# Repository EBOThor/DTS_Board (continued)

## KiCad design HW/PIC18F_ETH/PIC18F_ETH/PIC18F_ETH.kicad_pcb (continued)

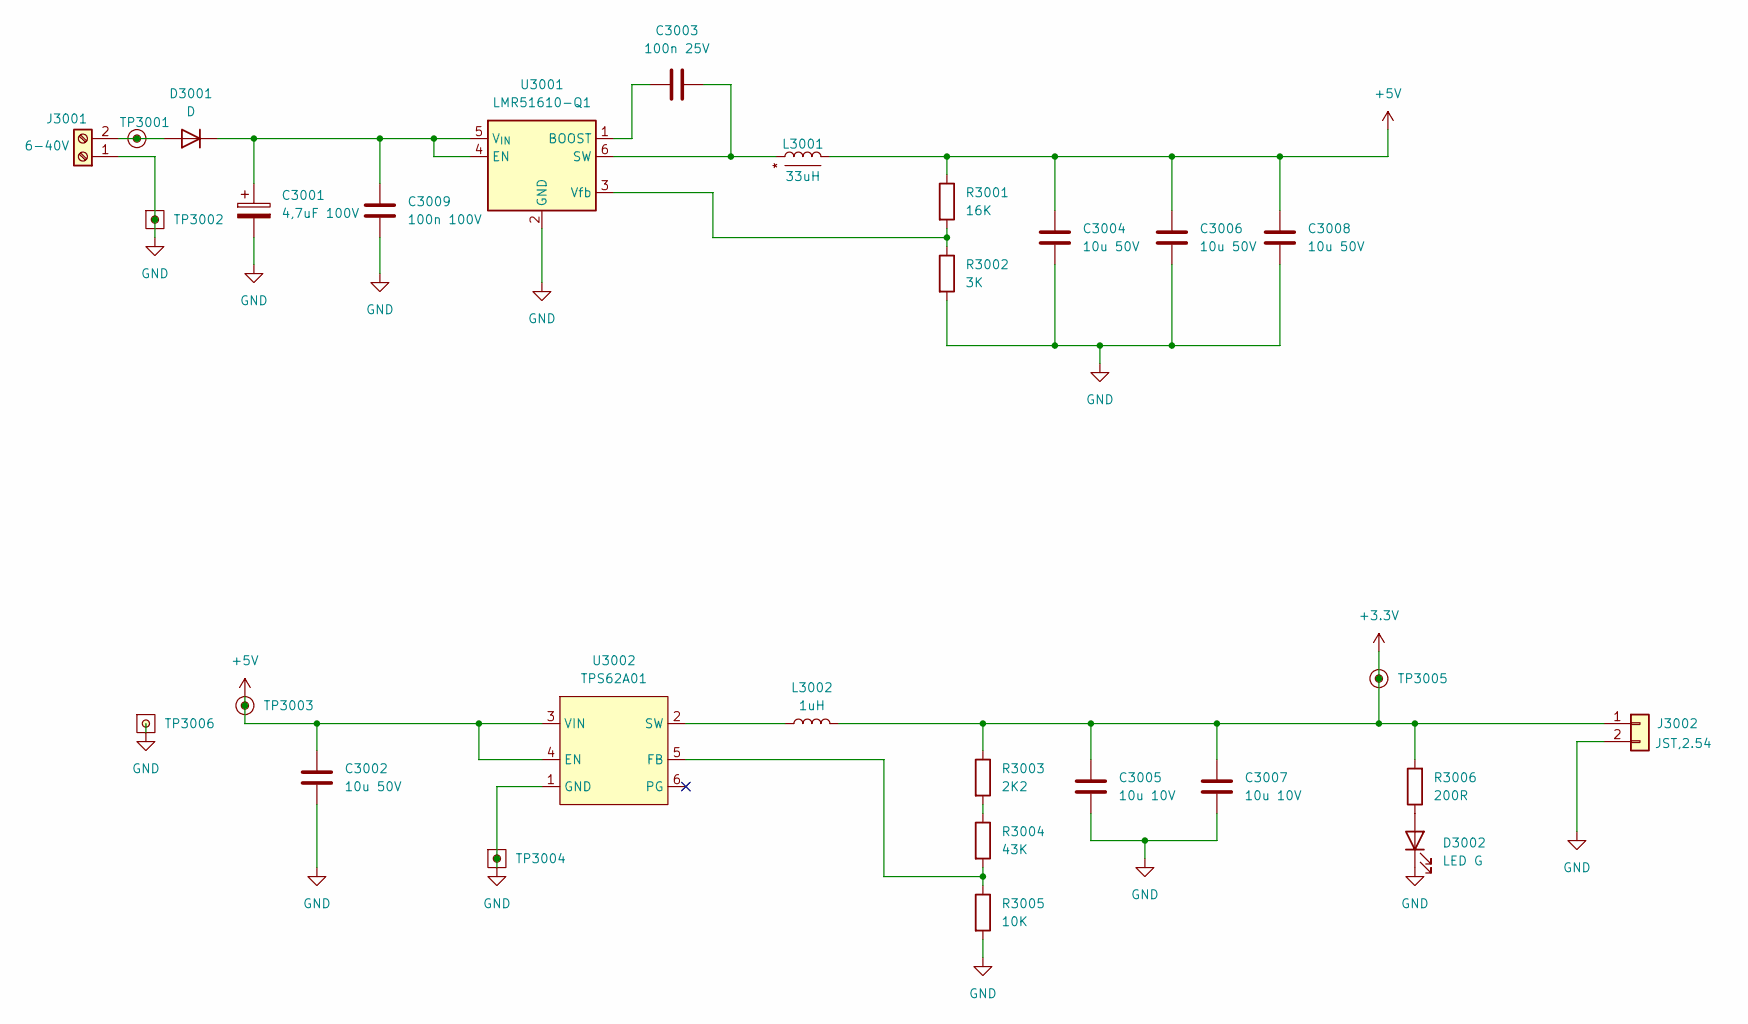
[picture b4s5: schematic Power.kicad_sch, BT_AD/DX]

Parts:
C3001: 4,7uF 100V; CP_Elec_4x3
C3002, C3004, C3006, C3008: 10u 50V; C_0603_1608Metric; MPN C;C;T1;S;P0603;NA
C3003: 100n 25V; C_0603_1608Metric; MPN C;C;T1;S;P0603;NA
C3005, C3007: 10u 10V; C_0603_1608Metric; MPN C;C;T1;S;P0603;NA
C3009: 100n 100V; C_0603_1608Metric; MPN C;M;100n;10p;100V;S;0603
D3001: D; D_0805_2012Metric
D3002: LED G; LED_0603_1608Metric; MPN D;LED;R;3V;25mA
J3001: 6-40V; Samtec_HPM-02-01-x-S_Straight_1x02_Pitch5.08mm
J3002: JST,2.54; JST_EH_B2B-EH-A_1x02_P2.50mm_Vertical; MPN JST 2 pin
L3001: 33uH; L_Bourns_SRR1208_12.7x12.7mm; MPN SRR1208-330YL
L3002: 1uH; L_0805_2012Metric; MPN CIGT201208EH1R0MNE
R3001: 16K; R_0603_1608Metric; MPN R;G;T1;S;P0603;NA
R3002: 3K; R_0603_1608Metric; MPN R;G;T1;S;P0603;NA
R3003: 2K2; R_0603_1608Metric; MPN R;G;T1;S;P0603;NA
R3004: 43K; R_0603_1608Metric; MPN R;G;T1;S;P0603;NA
R3005: 10K; R_0603_1608Metric; MPN R;G;T1;S;P0603;NA
R3006: 200R; R_0603_1608Metric; MPN R;G;T1;S;P0603;NA
TP3001, TP3003, TP3005: TestPoint; TestPoint_THTPad_D1.0mm_Drill0.5mm
TP3002, TP3004, TP3006: TestPoint; TestPoint_THTPad_1.0x1.0mm_Drill0.5mm
U3001: LMR51610-Q1; SOT-23-6; MPN LMR51610-Q1
U3002: TPS62A01; SOT-563; MPN TPS62A01

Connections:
+3.3V: C3005.1, C3007.1, J3002.1, L3002.2, R3003.1, R3006.2, TP3005.1; also elsewhere on the board
+5V: C3002.1, C3004.1, C3006.1, C3008.1, L3001.2, R3001.1, TP3003.1, U3002.3 (VIN), U3002.4 (EN); also elsewhere on the board
GND: C3001.2, C3002.2, C3004.2, C3005.2, C3006.2, C3007.2, C3008.2, C3009.2, D3002.1 (K), J3001.1, J3002.2, R3002.2, R3005.2, TP3002.1, TP3004.1, TP3006.1, U3001.2 (GND), U3002.1 (GND); also elsewhere on the board
unnamed: D3001.2 (A), J3001.2, TP3001.1
unnamed: C3001.1, C3009.1, D3001.1 (K), U3001.4 (EN), U3001.5 (V_{IN})
unnamed: D3002.2 (A), R3006.1
unnamed: R3003.2, R3004.1
unnamed: C3003.1, U3001.1 (BOOST)
unnamed: C3003.2, L3001.1, U3001.6 (SW)
unnamed: R3001.2, R3002.1, U3001.3 (Vfb)
unnamed: R3004.2, R3005.1, U3002.5 (FB)
unnamed: L3002.1, U3002.2 (SW)

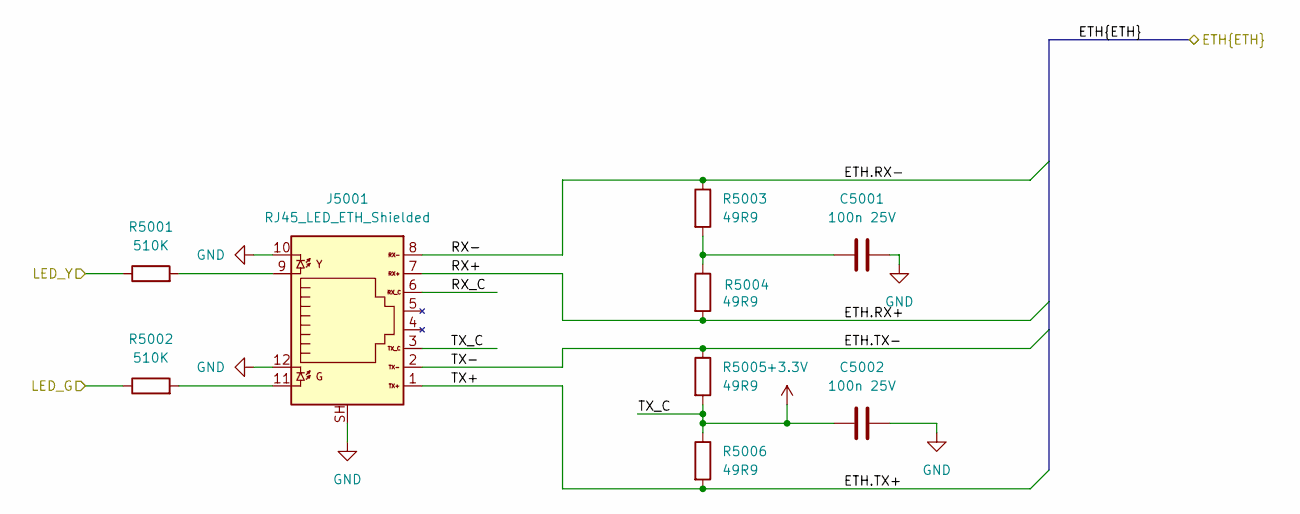
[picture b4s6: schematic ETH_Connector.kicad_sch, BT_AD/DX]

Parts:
C5001, C5002: 100n 25V; C_0603_1608Metric; MPN C;C;T1;S;P0603;NA
J5001: RJ45_LED_ETH_Shielded; RJ45_LED_Shield; MPN 41010276
R5001, R5002: 510K; R_0603_1608Metric; MPN R;G;T1;S;P0603;NA
R5003, R5004, R5005, R5006: 49R9; R_0603_1608Metric

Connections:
+3.3V: C5002.1, J5001.3, R5005.2, R5006.1; also elsewhere on the board
/ETH_Connector/ETH.RX+: J5001.7, R5004.2; also elsewhere on the board
/ETH_Connector/ETH.RX-: J5001.8, R5003.1; also elsewhere on the board
/ETH_Connector/ETH.TX+: J5001.1, R5006.2; also elsewhere on the board
/ETH_Connector/ETH.TX-: J5001.2, R5005.1; also elsewhere on the board
/ETH_Connector/RX_C: J5001.6
/LED_G: R5002.1; also elsewhere on the board
/LED_Y: R5001.1; also elsewhere on the board
GND: C5001.2, C5002.2, J5001.10, J5001.12, J5001.SH; also elsewhere on the board
unnamed: C5001.1, R5003.2, R5004.1
unnamed: J5001.9, R5001.2
unnamed: J5001.11, R5002.2

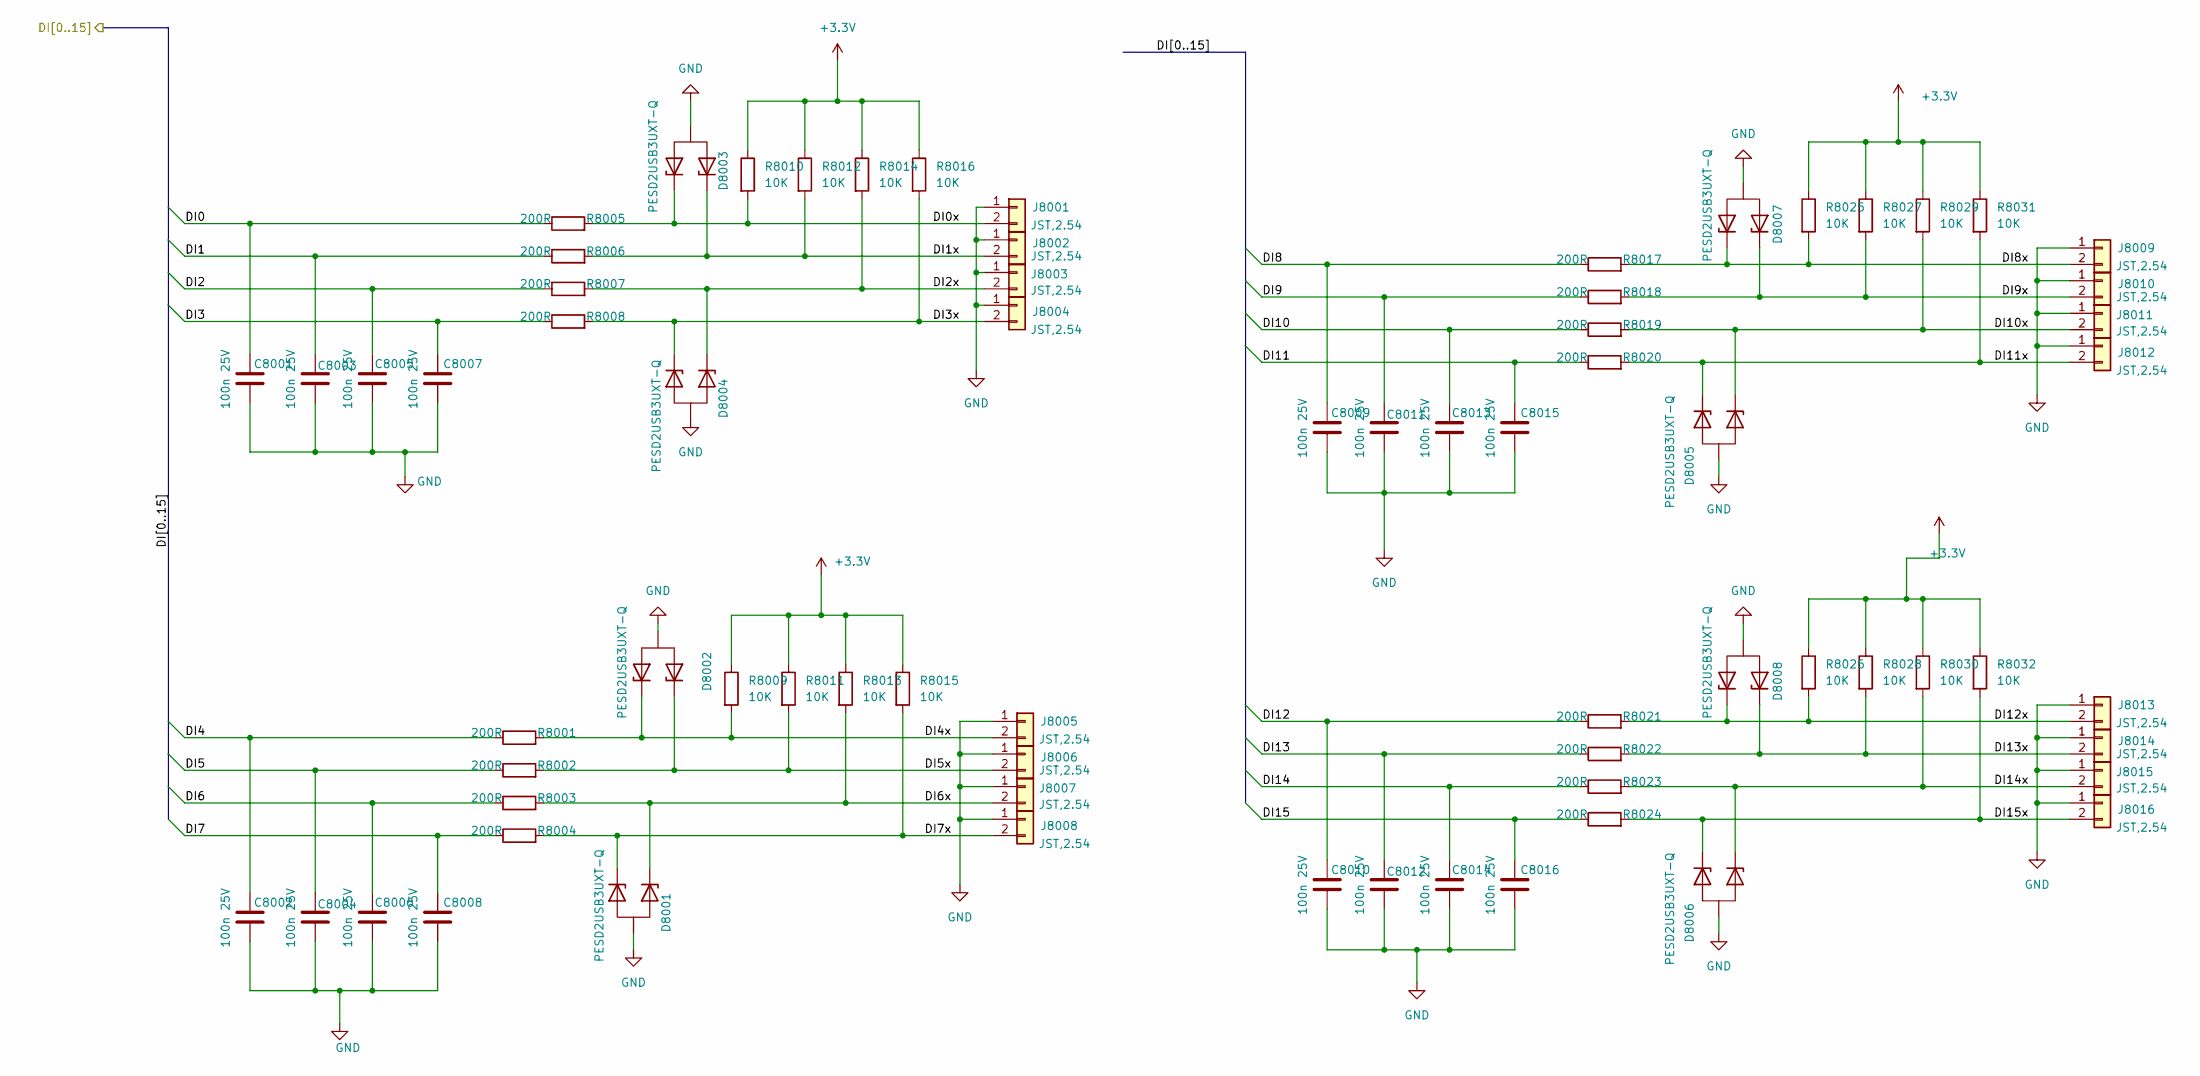
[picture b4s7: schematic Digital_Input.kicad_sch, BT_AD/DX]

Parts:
C8001, C8002, C8003, C8004, C8005, C8006, C8007, C8008, C8009, C8010, C8011, C8012, C8013, C8014, C8015, C8016: 100n 25V; C_0603_1608Metric; MPN C;C;T1;S;P0603;NA
D8001, D8002, D8003, D8004, D8005, D8006, D8007, D8008: PESD2USB3UXT-Q; SOT-23-3; MPN PESD2USB3UXT-Q
J8001, J8002, J8003, J8004, J8005, J8006, J8007, J8008, J8009, J8010, J8011, J8012, J8013, J8014, J8015, J8016: JST,2.54; JST_EH_B2B-EH-A_1x02_P2.50mm_Vertical; MPN JST 2 pin
R8001, R8002, R8003, R8004, R8005, R8006, R8007, R8008, R8017, R8018, R8019, R8020, R8021, R8022, R8023, R8024: 200R; R_0603_1608Metric; MPN R;G;T1;S;P0603;NA
R8009, R8010, R8011, R8012, R8013, R8014, R8015, R8016, R8025, R8026, R8027, R8028, R8029, R8030, R8031, R8032: 10K; R_0603_1608Metric; MPN R;G;T1;S;P0603;NA

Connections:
+3.3V: R8009.1, R8010.1, R8011.1, R8012.1, R8013.1, R8014.1, R8015.1, R8016.1, R8025.1, R8026.1, R8027.1, R8028.1, R8029.1, R8030.1, R8031.1, R8032.1; also elsewhere on the board
/IO_core/DI0: C8001.1, R8005.1; also elsewhere on the board
/IO_core/DI1: C8003.1, R8006.1; also elsewhere on the board
/IO_core/DI2: C8005.1, R8007.1; also elsewhere on the board
/IO_core/DI3: C8007.1, R8008.1; also elsewhere on the board
/IO_core/DI4: C8002.1, R8001.1; also elsewhere on the board
/IO_core/DI5: C8004.1, R8002.1; also elsewhere on the board
/IO_core/DI6: C8006.1, R8003.1; also elsewhere on the board
/IO_core/DI7: C8008.1, R8004.1; also elsewhere on the board
/IO_core/DI8: C8009.1, R8017.1; also elsewhere on the board
/IO_core/DI9: C8011.1, R8018.1; also elsewhere on the board
/IO_core/DI10: C8013.1, R8019.1; also elsewhere on the board
/IO_core/DI11: C8015.1, R8020.1; also elsewhere on the board
/IO_core/DI12: C8010.1, R8021.1; also elsewhere on the board
/IO_core/DI13: C8012.1, R8022.1; also elsewhere on the board
/IO_core/DI14: C8014.1, R8023.1; also elsewhere on the board
/IO_core/DI15: C8016.1, R8024.1; also elsewhere on the board
/IO_core/Digital Input/DI0x: D8003.1 (K1), J8001.2, R8005.2, R8010.2
/IO_core/Digital Input/DI1x: D8003.2 (K2), J8002.2, R8006.2, R8012.2
/IO_core/Digital Input/DI2x: D8004.1 (K1), J8003.2, R8007.2, R8014.2
/IO_core/Digital Input/DI3x: D8004.2 (K2), J8004.2, R8008.2, R8016.2
/IO_core/Digital Input/DI4x: D8002.1 (K1), J8005.2, R8001.2, R8009.2
/IO_core/Digital Input/DI5x: D8002.2 (K2), J8006.2, R8002.2, R8011.2
/IO_core/Digital Input/DI6x: D8001.1 (K1), J8007.2, R8003.2, R8013.2
/IO_core/Digital Input/DI7x: D8001.2 (K2), J8008.2, R8004.2, R8015.2
/IO_core/Digital Input/DI8x: D8007.1 (K1), J8009.2, R8017.2, R8025.2
/IO_core/Digital Input/DI9x: D8007.2 (K2), J8010.2, R8018.2, R8027.2
/IO_core/Digital Input/DI10x: D8005.1 (K1), J8011.2, R8019.2, R8029.2
/IO_core/Digital Input/DI11x: D8005.2 (K2), J8012.2, R8020.2, R8031.2
/IO_core/Digital Input/DI12x: D8008.1 (K1), J8013.2, R8021.2, R8026.2
/IO_core/Digital Input/DI13x: D8008.2 (K2), J8014.2, R8022.2, R8028.2
/IO_core/Digital Input/DI14x: D8006.1 (K1), J8015.2, R8023.2, R8030.2
/IO_core/Digital Input/DI15x: D8006.2 (K2), J8016.2, R8024.2, R8032.2
GND: C8001.2, C8002.2, C8003.2, C8004.2, C8005.2, C8006.2, C8007.2, C8008.2, C8009.2, C8010.2, C8011.2, C8012.2, C8013.2, C8014.2, C8015.2, C8016.2, D8001.3 (CA), D8002.3 (CA), D8003.3 (CA), D8004.3 (CA), D8005.3 (CA), D8006.3 (CA), D8007.3 (CA), D8008.3 (CA), J8001.1, J8002.1, J8003.1, J8004.1, J8005.1, J8006.1, J8007.1, J8008.1, J8009.1, J8010.1, J8011.1, J8012.1, J8013.1, J8014.1, J8015.1, J8016.1; also elsewhere on the board

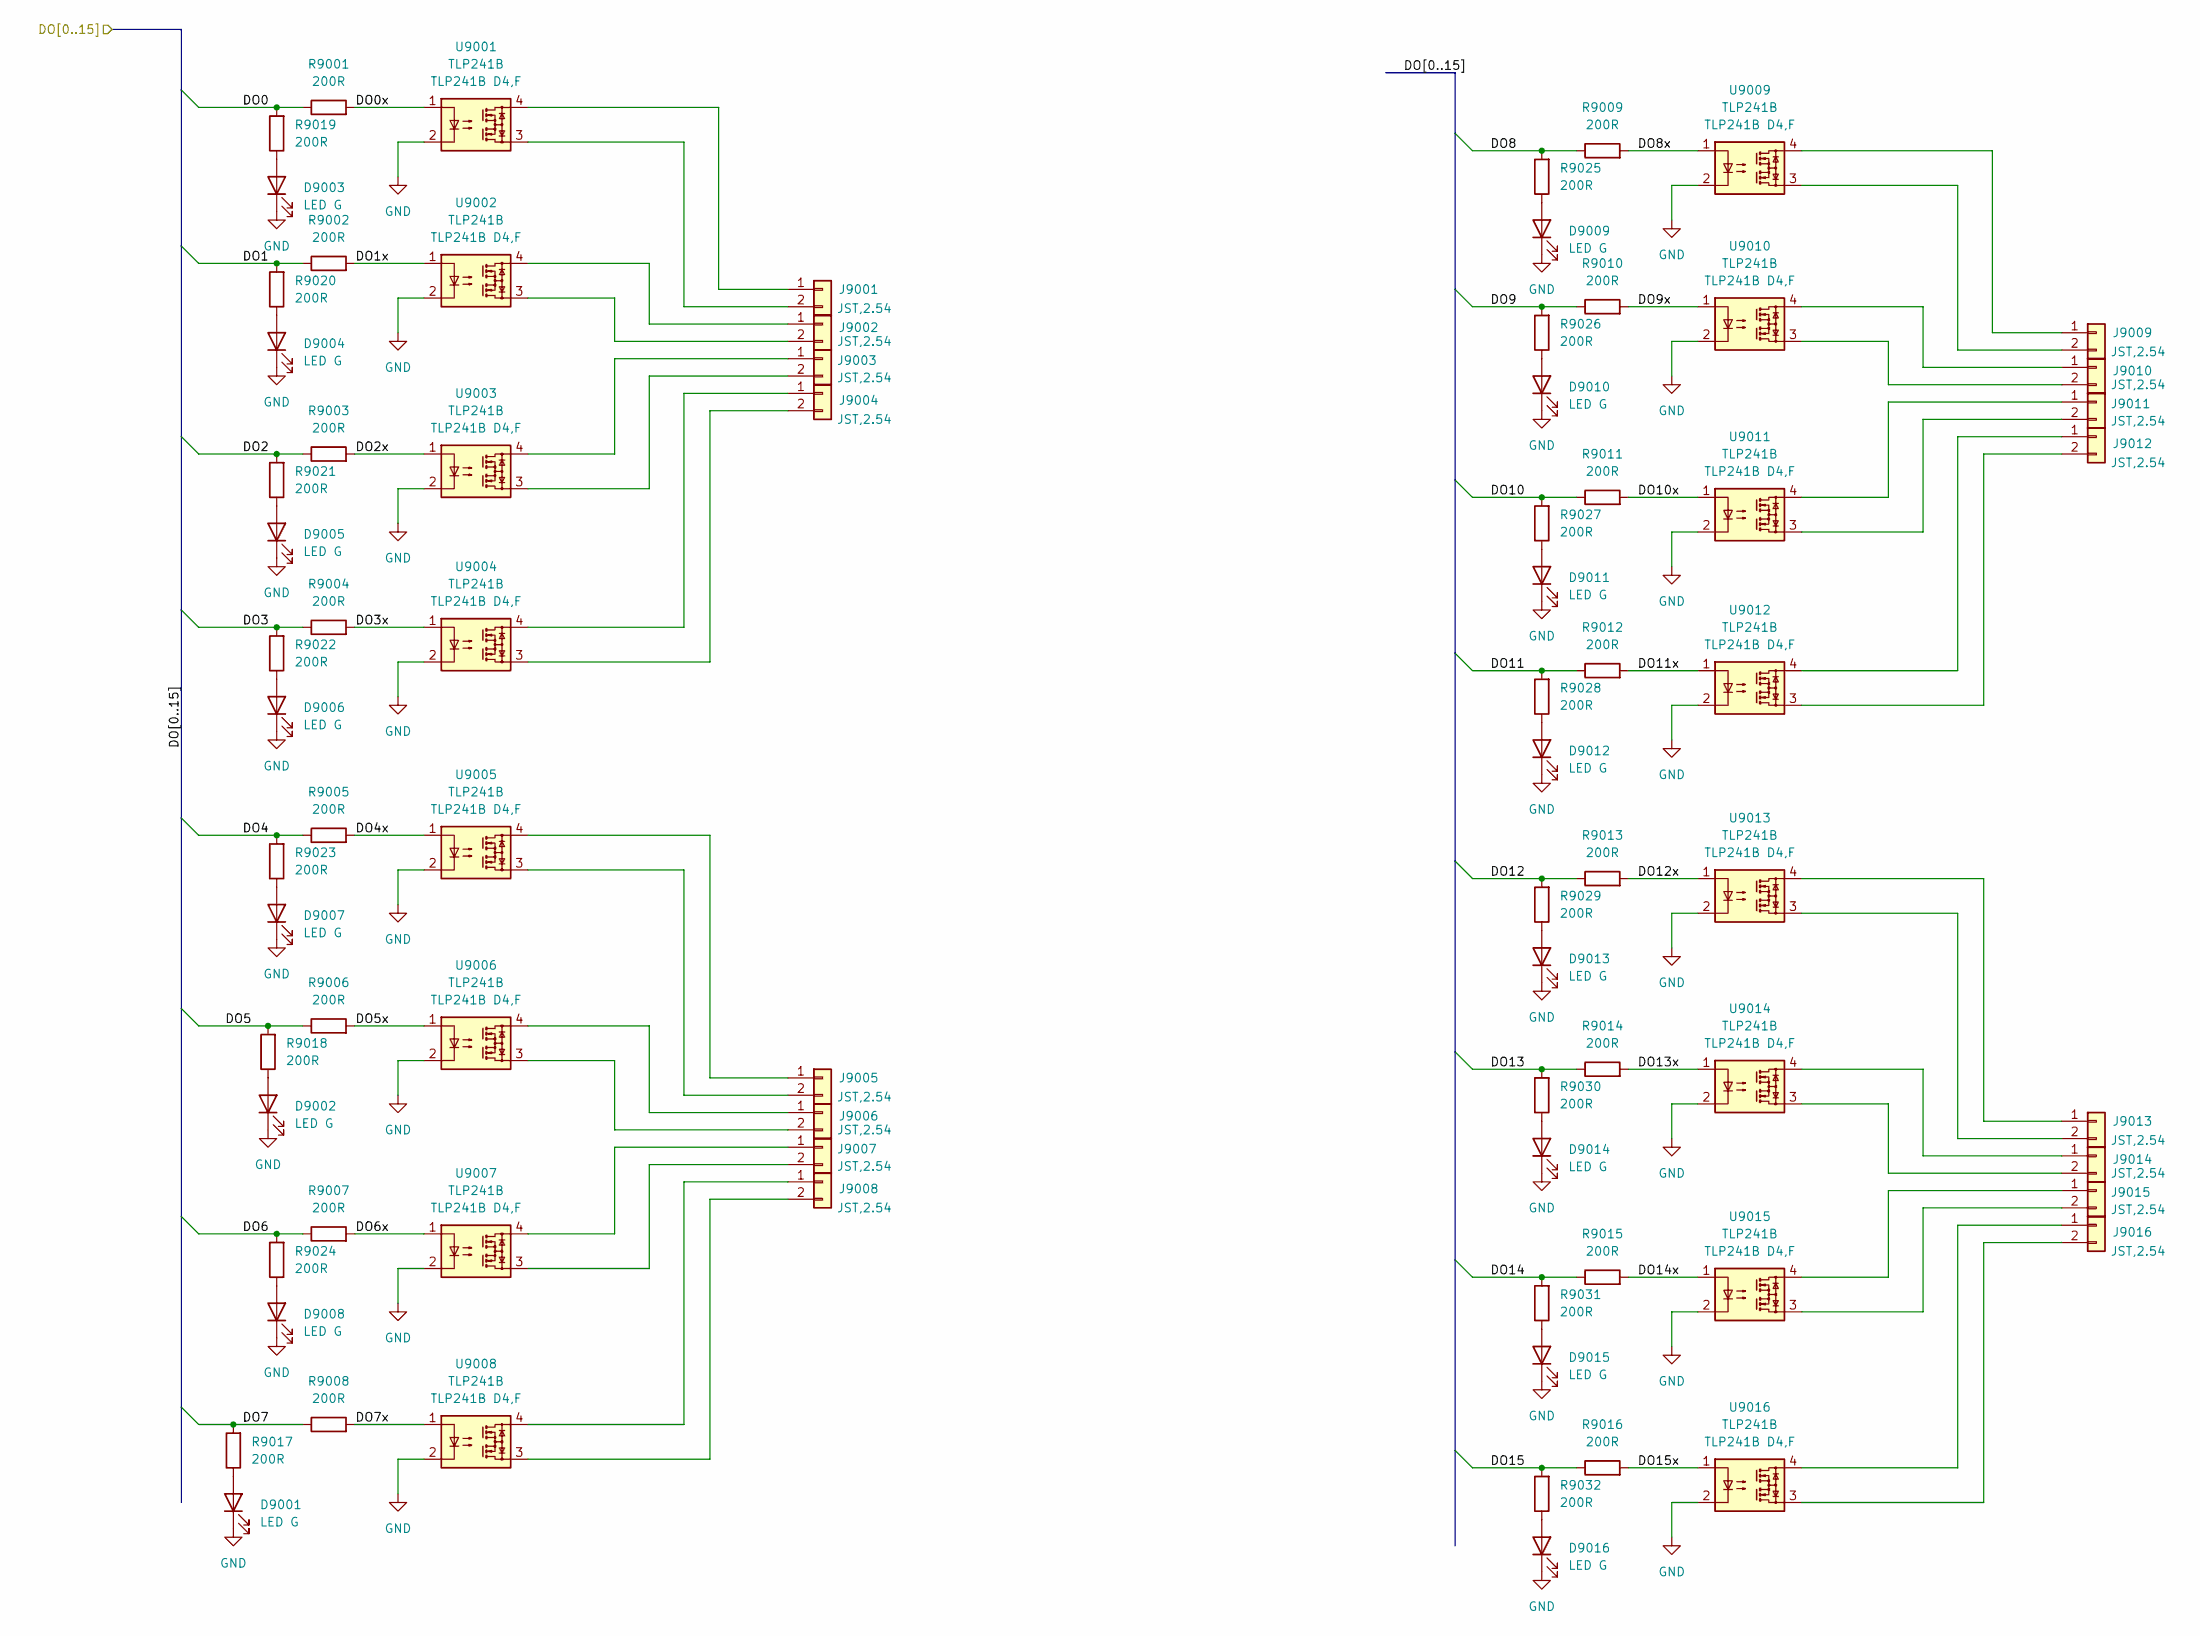
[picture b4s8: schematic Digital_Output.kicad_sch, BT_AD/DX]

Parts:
D9001, D9002, D9003, D9004, D9005, D9006, D9007, D9008, D9009, D9010, D9011, D9012, D9013, D9014, D9015, D9016: LED G; LED_0603_1608Metric; MPN D;LED;R;3V;25mA
J9001, J9002, J9003, J9004, J9005, J9006, J9007, J9008, J9009, J9010, J9011, J9012, J9013, J9014, J9015, J9016: JST,2.54; JST_EH_B2B-EH-A_1x02_P2.50mm_Vertical; MPN JST 2 pin
R9001, R9002, R9003, R9004, R9005, R9006, R9007, R9008, R9009, R9010, R9011, R9012, R9013, R9014, R9015, R9016, R9017, R9018, R9019, R9020, R9021, R9022, R9023, R9024, R9025, R9026, R9027, R9028, R9029, R9030, R9031, R9032: 200R; R_0603_1608Metric; MPN R;G;T1;S;P0603;NA
U9001, U9002, U9003, U9004, U9005, U9006, U9007, U9008, U9009, U9010, U9011, U9012, U9013, U9014, U9015, U9016: TLP241B; SO-4_7.6x3.6mm_P2.54mm; MPN TLP241B D4,F

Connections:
/IO_core/DO0: R9001.1, R9019.2; also elsewhere on the board
/IO_core/DO1: R9002.1, R9020.2; also elsewhere on the board
/IO_core/DO2: R9003.1, R9021.2; also elsewhere on the board
/IO_core/DO3: R9004.1, R9022.2; also elsewhere on the board
/IO_core/DO4: R9005.1, R9023.2; also elsewhere on the board
/IO_core/DO5: R9006.1, R9018.2; also elsewhere on the board
/IO_core/DO6: R9007.1, R9024.2; also elsewhere on the board
/IO_core/DO7: R9008.1, R9017.2; also elsewhere on the board
/IO_core/DO8: R9009.1, R9025.2; also elsewhere on the board
/IO_core/DO9: R9010.1, R9026.2; also elsewhere on the board
/IO_core/DO10: R9011.1, R9027.2; also elsewhere on the board
/IO_core/DO11: R9012.1, R9028.2; also elsewhere on the board
/IO_core/DO12: R9013.1, R9029.2; also elsewhere on the board
/IO_core/DO13: R9014.1, R9030.2; also elsewhere on the board
/IO_core/DO14: R9015.1, R9031.2; also elsewhere on the board
/IO_core/DO15: R9016.1, R9032.2; also elsewhere on the board
/IO_core/Digital Output/DO0x: R9001.2, U9001.1
/IO_core/Digital Output/DO1x: R9002.2, U9002.1
/IO_core/Digital Output/DO2x: R9003.2, U9003.1
/IO_core/Digital Output/DO3x: R9004.2, U9004.1
/IO_core/Digital Output/DO4x: R9005.2, U9005.1
/IO_core/Digital Output/DO5x: R9006.2, U9006.1
/IO_core/Digital Output/DO6x: R9007.2, U9007.1
/IO_core/Digital Output/DO7x: R9008.2, U9008.1
/IO_core/Digital Output/DO8x: R9009.2, U9009.1
/IO_core/Digital Output/DO9x: R9010.2, U9010.1
/IO_core/Digital Output/DO10x: R9011.2, U9011.1
/IO_core/Digital Output/DO11x: R9012.2, U9012.1
/IO_core/Digital Output/DO12x: R9013.2, U9013.1
/IO_core/Digital Output/DO13x: R9014.2, U9014.1
/IO_core/Digital Output/DO14x: R9015.2, U9015.1
/IO_core/Digital Output/DO15x: R9016.2, U9016.1
GND: D9001.1 (K), D9002.1 (K), D9003.1 (K), D9004.1 (K), D9005.1 (K), D9006.1 (K), D9007.1 (K), D9008.1 (K), D9009.1 (K), D9010.1 (K), D9011.1 (K), D9012.1 (K), D9013.1 (K), D9014.1 (K), D9015.1 (K), D9016.1 (K), U9001.2, U9002.2, U9003.2, U9004.2, U9005.2, U9006.2, U9007.2, U9008.2, U9009.2, U9010.2, U9011.2, U9012.2, U9013.2, U9014.2, U9015.2, U9016.2; also elsewhere on the board
unnamed: D9001.2 (A), R9017.1
unnamed: D9002.2 (A), R9018.1
unnamed: D9003.2 (A), R9019.1
unnamed: D9004.2 (A), R9020.1
unnamed: D9005.2 (A), R9021.1
unnamed: D9006.2 (A), R9022.1
unnamed: D9007.2 (A), R9023.1
unnamed: D9008.2 (A), R9024.1
unnamed: D9009.2 (A), R9025.1
unnamed: D9010.2 (A), R9026.1
unnamed: D9011.2 (A), R9027.1
unnamed: D9012.2 (A), R9028.1
unnamed: D9013.2 (A), R9029.1
unnamed: D9014.2 (A), R9030.1
unnamed: D9015.2 (A), R9031.1
unnamed: D9016.2 (A), R9032.1
unnamed: J9001.1, U9001.4
unnamed: J9001.2, U9001.3
unnamed: J9002.1, U9002.4
unnamed: J9002.2, U9002.3
unnamed: J9003.1, U9003.4
unnamed: J9003.2, U9003.3
unnamed: J9004.1, U9004.4
unnamed: J9004.2, U9004.3
unnamed: J9005.1, U9005.4
unnamed: J9005.2, U9005.3
unnamed: J9006.1, U9006.4
unnamed: J9006.2, U9006.3
unnamed: J9007.1, U9007.4
unnamed: J9007.2, U9007.3
unnamed: J9008.1, U9008.4
unnamed: J9008.2, U9008.3
unnamed: J9009.1, U9009.4
unnamed: J9009.2, U9009.3
unnamed: J9010.1, U9010.4
unnamed: J9010.2, U9010.3
unnamed: J9011.1, U9011.4
unnamed: J9011.2, U9011.3
unnamed: J9012.1, U9012.4
unnamed: J9012.2, U9012.3
unnamed: J9013.1, U9013.4
unnamed: J9013.2, U9013.3
unnamed: J9014.1, U9014.4
unnamed: J9014.2, U9014.3
unnamed: J9015.1, U9015.4
unnamed: J9015.2, U9015.3
unnamed: J9016.1, U9016.4
unnamed: J9016.2, U9016.3

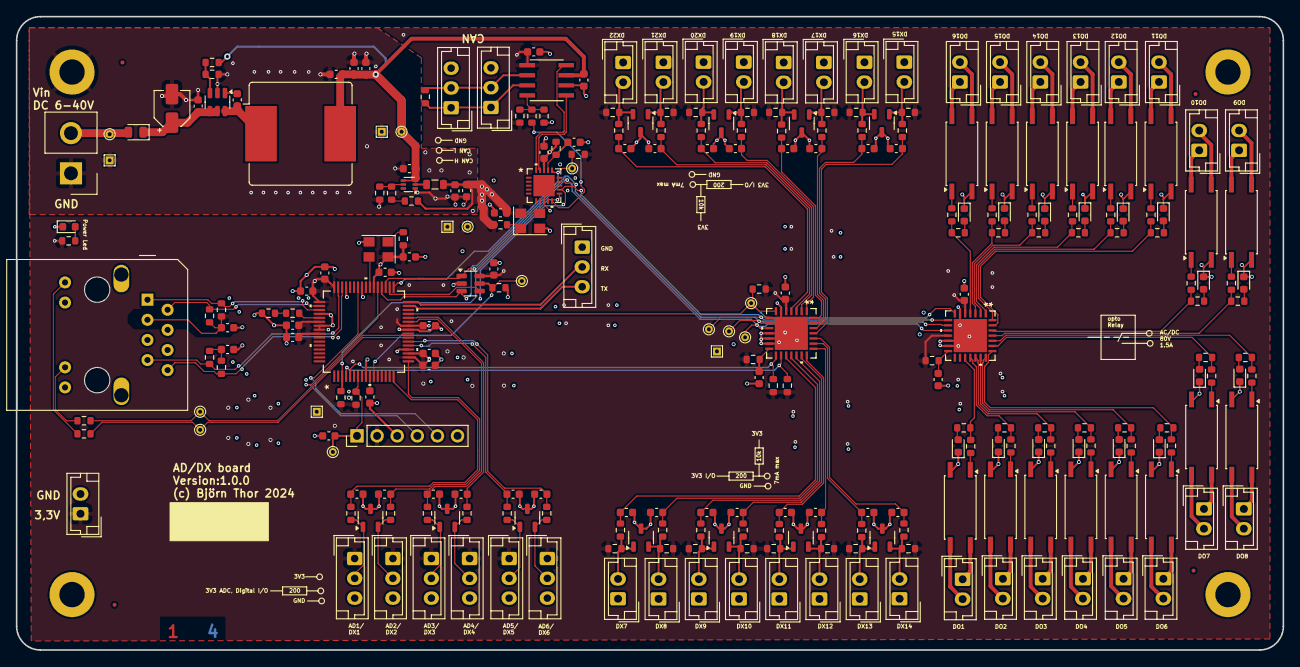
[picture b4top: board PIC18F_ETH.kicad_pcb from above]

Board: 4 copper layers, 160.0 x 80.0 mm, 281 parts (0 on the bottom side), 175 nets.

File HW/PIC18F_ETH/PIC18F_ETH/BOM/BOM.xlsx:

Reference | Value | Qty | DNP | # | CPN | MPN | Footprint | DigiKey | Column1 | Cart
R3006,R4001,R4002,R4003,R4004,R4005,R4006,R8001,R8002,R8003,R8004,R8005,R8006,R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 | 200R | 55 |  | 1 | BT00002-02000 | R;G;200R;10P0;S;0603 | Resistor_SMD:R_0603_1608Metric | 311-200HRCT-ND | RC0603FR-07200RL | x
C2001,C2002,C2003,C2004,C2005,C2006,C2007,C2008,C2009,C2010,C2012,C3003,C4001,C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 | 100n 25V | 45 |  | 2 | BT00008-090680 | C;M;100n;10p;25V;S;0603 | Capacitor_SMD:C_0603_1608Metric
J3002,J8001,J8002,J8003,J8004,J8005,J8006,J8007,J8008,J8009,J8010,J8011,J8012,J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 | JST,2.54 | 33 |  | 3 | BT10003-00002 | JST 2 pin | Connector_JST:JST_EH_B2B-EH-A_1x02_P2.50mm_Vertical
R2001,R2002,R2004,R2006,R2007,R2008,R2009,R2010,R3005,R4007,R4008,R6001,R6002,R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 | 10K | 30 |  | 4 | BT00002-30100 | R;G;10K;10P0;S;0603 | Resistor_SMD:R_0603_1608Metric | 311-10.0KHRCT-ND | RC0603FR-0710KL | x
TP2001,TP2002,TP2005,TP2006,TP2007,TP2008,TP2009,TP2010,TP2011,TP2012,TP2016,TP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 | TestPoint | 17 |  | 5 |  |  | -- mixed values --
D3002,D9001,D9002,D9003,D9004,D9005,D9006,D9007,D9008,D9009,D9010,D9011,D9012,D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 | LED G | 17 |  | 6 | BT13001-00001 | D;LED;R;3V;25mA | LED_SMD:LED_0603_1608Metric
U9001,U9002,U9003,U9004,U9005,U9006,U9007,U9008,U9009,U9010,U9011,U9012,U9013,U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 | TLP241B | 16 |  | 7 | BT11001-00001 | TLP241B D4,F | Package_SO:SO-4_7.6x3.6mm_P2.54mm | 264-TLP241BP | TLP241BP(D4TP1,E(O
D4001,D4002,D4003,D8001,D8002,D8003,D8004,D8005,D8006,D8007,D8008 | PESD2USB3UXT-Q | 11 |  | 8 | BT09002-00001 | PESD2USB3UXT-Q | Package_TO_SOT_SMD:SOT-23-3
J2002,J4001,J4002,J4003,J4004,J4005,J4006,J6001,J6002 | JST,2.54 | 9 |  | 9 | BT10003-00003 | JST 3 pin | Connector_JST:JST_EH_B3B-EH-A_1x03_P2.50mm_Vertical
R5003,R5004,R5005,R5006 | 49R9 | 4 |  | 10 |  |  | Resistor_SMD:R_0603_1608Metric | 311-49.9HRCT-ND | RC0603FR-0749R9L
C3002,C3004,C3006,C3008 | 10u 50V | 4 |  | 11 | BT00007-060100 | C;M;10u;10p;50V;S;0603 | Capacitor_SMD:C_0603_1608Metric
C2011,C3005,C3007 | 10u 10V | 3 |  | 12 | BT00010-060100 | C;M;10u;10p;10V;S;0603 | Capacitor_SMD:C_0603_1608Metric
U4001,U4002 | MCP23S17-E/ML | 2 |  | 13 | BT02009-00001 | MCP23S17-E_ML | bt_footprints:QFN28_6x6MC_MCH | MCP23S17T-E/MLCT-ND | MCP23S17T-E/ML | x
U2003,U6001 | 25Mhz,50ppm | 2 |  | 14 | BT05001-25601 | SG3225CAN 25.0000M-TJGA6 | Oscillator:Oscillator_SMD_SeikoEpson_SG8002CE-4Pin_3.2x2.5mm | 114-SG3225CAN25.0000M-TJGA6CT-ND | SG3225CAN 25.0000M-TJGA6 | x
R5001,R5002 | 510K | 2 |  | 15 | BT00002-35100 | R;G;510K;10P0;S;0603 | Resistor_SMD:R_0603_1608Metric | 311-510KHRCT-ND | RC0603FR-07510KL | x
R2003,R3003 | 2K2 | 2 |  | 16 | BT00002-30022 | R;G;2K2;10P0;S;0603 | Resistor_SMD:R_0603_1608Metric | 311-2.20KHRCT-ND | RC0603FR-072K2L | x
U6003 | ATA6561-GAQW | 1 |  | 17 | BT02007-00001 | ATA6561-GAQW | bt_footprints:SOIC8_4P9X3P9MC_MCH | ATA6561-GAQW-NCT-ND | ATA6561-GAQW-N | x
U6002 | MCP2515T-E/ML | 1 |  | 18 | BT02006-00001 MCP2515 | MCP2515T-E/ML | bt_footprints:QFN20_4x4MC_MCH | MCP2515-E/ML-ND | MCP2515-E/ML | x
U3002 | TPS62A01 | 1 |  | 19 | BT03005-00001 | TPS62A01 | Package_TO_SOT_SMD:SOT-563 | 296-TPS62A01DRLRCT-ND | TPS62A01DRLR | x
U3001 | LMR51610-Q1 | 1 |  | 20 | BT03009-00001 | LMR51610-Q1 | Package_TO_SOT_SMD:SOT-23-6 | 296-LMR51610YFDBVRCT-ND | LMR51610YFDBVR | x
U2002 | PIC18F67J60T-I | 1 |  | 21 | BT01004-00001 | PIC18F67J60T-I/PT | bt_footprints:TQFP64_10x10MC_MCH | PIC18F67J60T-I/PTCT-ND | PIC18F67J60T-I/PT | x
U2001 | 93AA46BT-I/OT | 1 |  | 22 | BT07001-00001 | 93AA46BT-I/OT | Package_TO_SOT_SMD:SOT-23-6 | 93AA46BT-I/OTCT-ND | 93AA46BT-I/OT | x
R6006 | 120R | 1 | DNP | 23 | BT00002-01200 | R;G;120R;10P0;S;0603 | Resistor_SMD:R_0603_1608Metric
R6004 | 0R | 1 | DNP | 24 | BT00002-00000 | R;G;0R;10P0;S;0603 | Resistor_SMD:R_0603_1608Metric | 311-0.0HRCT-ND | RC0603FR-070RL | x
R6003 | 0R | 1 |  | 25 | BT00002-00000 | R;G;0R;10P0;S;0603 | Resistor_SMD:R_0603_1608Metric | 311-0.0HRCT-ND | RC0603FR-070RL | x
R3004 | 43K | 1 |  | 26 | BT00002-30430 | R;G;43K;10P0;S;0603 | Resistor_SMD:R_0603_1608Metric | 311-43.0KHRCT-ND | RC0603FR-0743KL | x
R3002 | 3K | 1 |  | 27 | BT00002-30030 | R;G;3K;10P0;S;0603 | Resistor_SMD:R_0603_1608Metric | 311-3.00KHRCT-ND | RC0603FR-073KL | x
R3001 | 16K | 1 |  | 28 | BT00002-30160 | R;G;16K;10P0;S;0603 | Resistor_SMD:R_0603_1608Metric | 311-16.0KHRCT-ND | RC0603FR-0716KL | x
R2005 | 620R | 1 |  | 29 | BT00002-06200 | R;G;620R;10P0;S;0603 | Resistor_SMD:R_0603_1608Metric | 311-620HRCT-ND | RC0603FR-07620RL | x
L3002 | 1uH | 1 |  | 30 | BT00200-00001 | CIGT201208EH1R0MNE | Inductor_SMD:L_0805_2012Metric | 1276-6886-1-ND | CIGT201208EH1R0MNE | x
L3001 | 33uH | 1 |  | 31 | BT00201-33028 | SRR1208-330YL | Inductor_SMD:L_Bourns_SRR1208_12.7x12.7mm | 118-SRR1208-330YLCT-ND | SRR1208-330YL | x
J5001 | RJ45_LED_ETH_Shielded | 1 |  | 32 | BT10000-00001 | 41010276 | bt_footprints:RJ45_LED_Shield
J3001 | 6-40V | 1 |  | 33 |  |  | Connector_Samtec_HPM_THT:Samtec_HPM-02-01-x-S_Straight_1x02_Pitch5.08mm
J2001 | Conn_01x06 | 1 |  | 34 |  |  | Connector_PinHeader_2.54mm:PinHeader_1x06_P2.54mm_Vertical | 732-2070-ND
D3001 | D | 1 |  | 35 |  |  | Diode_SMD:D_0805_2012Metric
C3009 | 100n 100V | 1 |  | 36 | BT00013-090680 | C;M;100n;10p;100V;S;0603 | Capacitor_SMD:C_0603_1608Metric
C3001 | 4,7uF 100V | 1 |  | 37 |  |  | Capacitor_SMD:CP_Elec_4x3
